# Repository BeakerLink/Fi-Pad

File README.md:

# Fi-Pad

This is my take on the HackPad for the 2025 Hack Club. It features 9 programable keys, and a 0.91 in OLED screen

## Design

I designed the PCB using Ki-Cad, and designed the case in OnShape

Onshape Link:
https://cad.onshape.com/documents/796c38b270e72c4871a9677c/w/28c50ec203dddb21f0b40055/e/97d6ca14d4db237f55ec0b99?renderMode=0&uiState=685f30195171274e6eff8953

### PCB schematic

### PCB layout

### Full Case

### Top Case

### Base Case

# Firmware Overview

The firmware is still in development, I plan to update this once I have a semifunctional build. It will be based around QKM, and use VIA for dynamic changes.

# BOM

* 1x Xiao RP2040
* 1x 0.91 in OLED display
* 1x PCB
* 9x MX keyboard Switchs
* 9x DSA Keycaps
* 4x M3x5mx4mm Heat Set Inserts
* 4x M3x16 Screws
* 1x 3D printed Top Shell
* 1x 3D printed Base Shell

# What's in a name
I named this project the "Fi-Pad" for two reasons. First of all, some backstory. My name is Link, and with that has come a healthy obsession with "The Ledgend of Zelda" In the games there is a reoccuring item called "The Master Sword." Inside the sword dwells a spirit named "Fi" Which was appointed by the goddess to Assist "Link" In their journey. Bringing this Back to me, I nicknamed my laptop "Fi" because of how it assists me through my journey. And the other reason I named the project "Fi-Pad" is a play on Apple's iPad.

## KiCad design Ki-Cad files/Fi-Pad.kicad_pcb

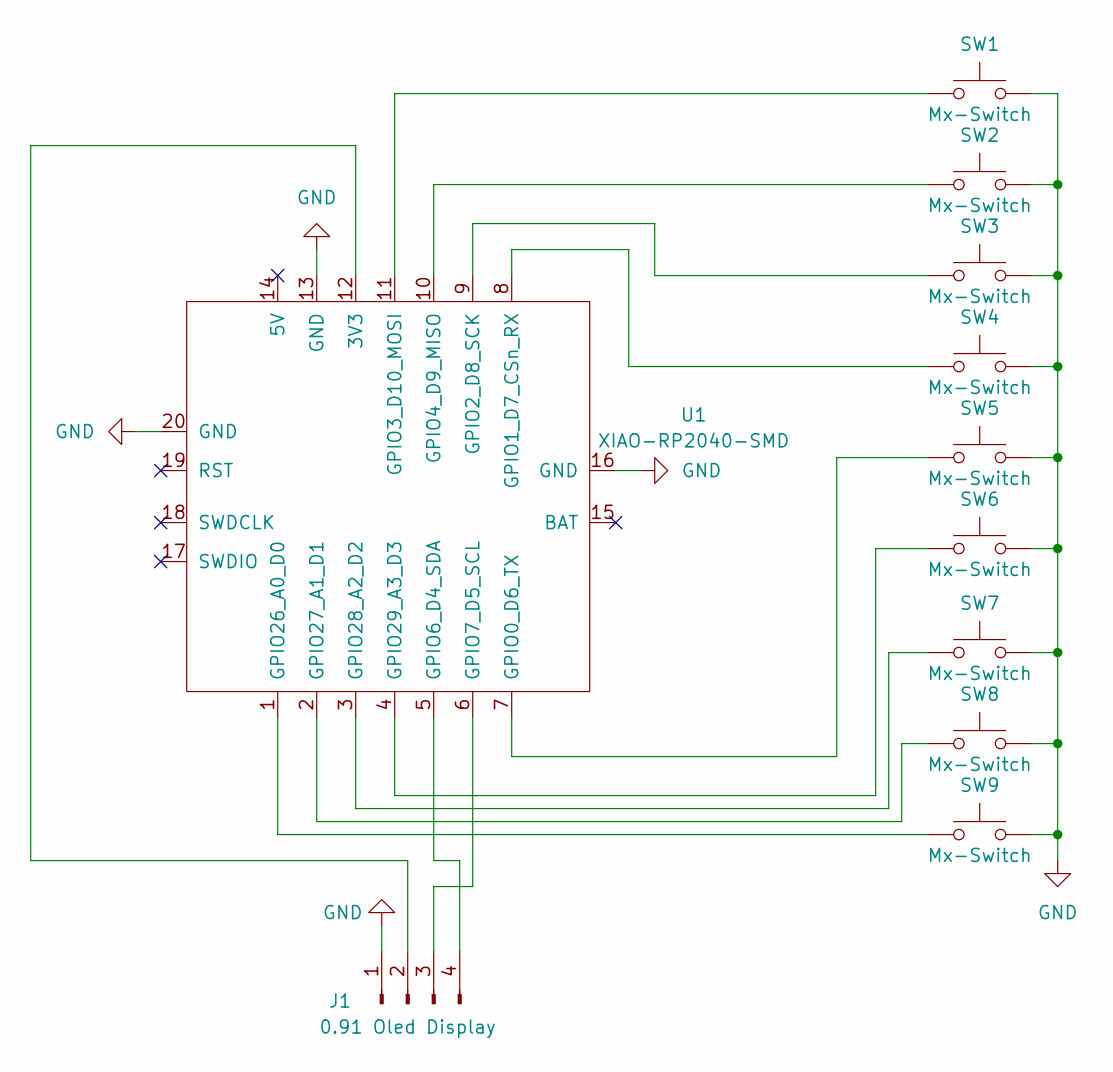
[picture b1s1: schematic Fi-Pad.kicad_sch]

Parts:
J1: 0.91 Oled Display; PinSocket_1x04_P2.00mm_Vertical
SW1, SW2, SW3, SW4, SW5, SW6, SW7, SW8, SW9: Mx-Switch; SW_Cherry_MX_PCB_1.00u
U1: XIAO-RP2040-SMD

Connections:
GND: J1.1, SW1.2, SW2.2, SW3.2, SW4.2, SW5.2, SW6.2, SW7.2, SW8.2, SW9.2, U1.13 (GND), U1.16 (GND), U1.20 (GND)
unnamed: J1.2, U1.12 (3V3)
unnamed: J1.3, U1.6 (GPIO7_D5_SCL)
unnamed: J1.4, U1.5 (GPIO6_D4_SDA)
unnamed: SW5.1, U1.7 (GPIO0_D6_TX)
unnamed: SW4.1, U1.8 (GPIO1_D7_CSn_RX)
unnamed: SW3.1, U1.9 (GPIO2_D8_SCK)
unnamed: SW1.1, U1.11 (GPIO3_D10_MOSI)
unnamed: SW2.1, U1.10 (GPIO4_D9_MISO)
unnamed: SW9.1, U1.1 (GPIO26_A0_D0)
unnamed: SW8.1, U1.2 (GPIO27_A1_D1)
unnamed: SW7.1, U1.3 (GPIO28_A2_D2)
unnamed: SW6.1, U1.4 (GPIO29_A3_D3)

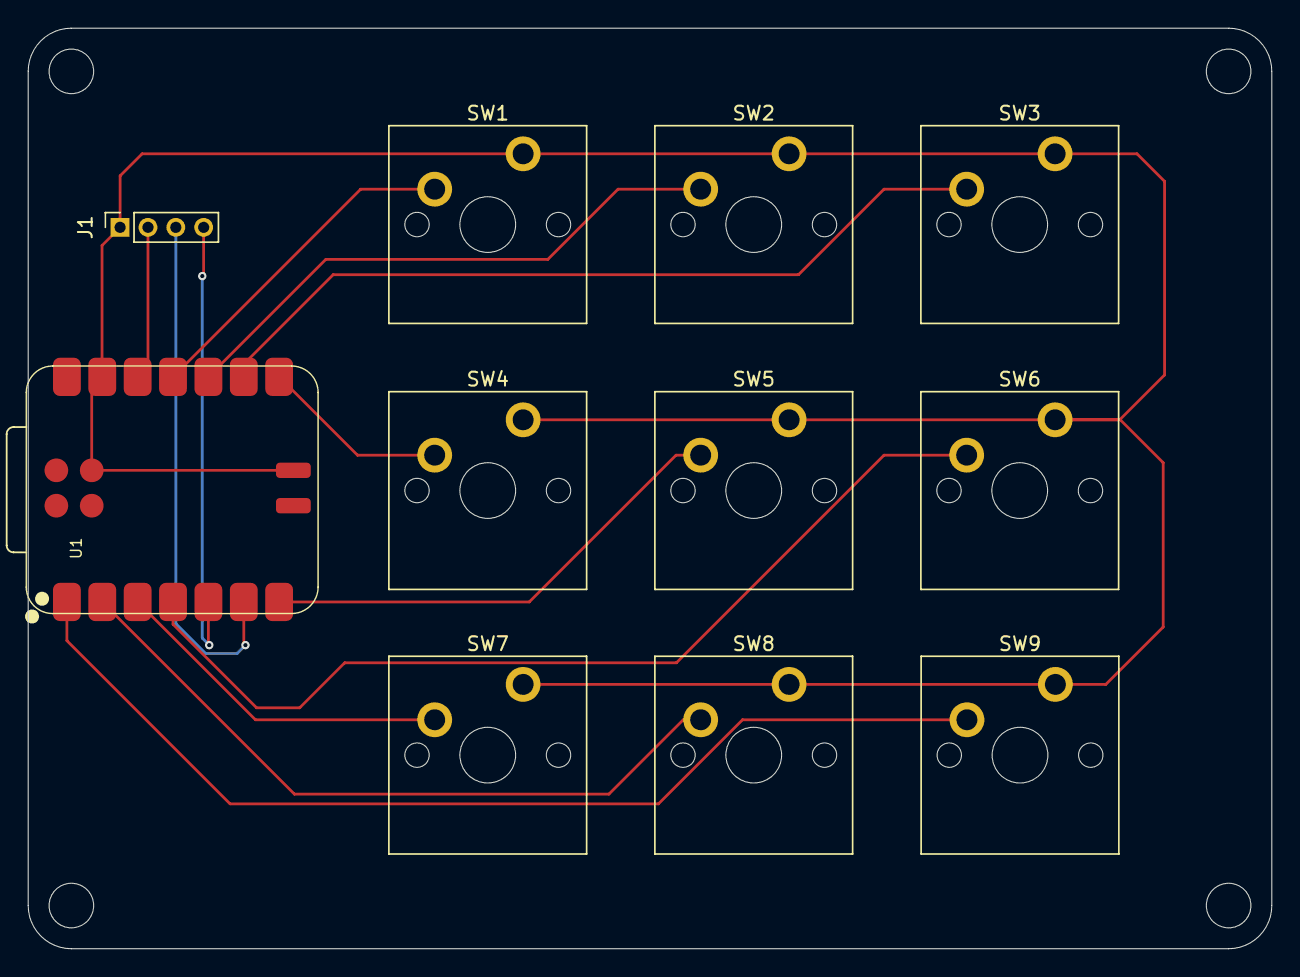
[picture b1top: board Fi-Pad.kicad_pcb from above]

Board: 2 copper layers, 89.3 x 66.1 mm, 11 parts (0 on the bottom side), 13 nets.

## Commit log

2025-06-27 CAD Files
2025-06-27 Moved CAD files to folder
2025-06-27 KiCad Files
2025-06-27 Add README.md and Ki cad files
2025-06-27 Add Gerbers.zip
2025-06-27 Light trimming
2025-06-27 Adding Assets for README.md
2025-06-27 Adding Assets for README.md Number 2 electric boogaloo
2025-06-27 Code? On Github? What is this world coming too
2025-06-28 Started on README.md
2025-06-28 More stuff to READ.md
2025-06-28 God I suck at spelling/Grammar
2025-06-29 Updating photos to fix my mistake
2025-06-29 Putting new photos into README.md
2025-06-29 Updating Ki-CAD files
2025-06-29 Updating Gerber Files
